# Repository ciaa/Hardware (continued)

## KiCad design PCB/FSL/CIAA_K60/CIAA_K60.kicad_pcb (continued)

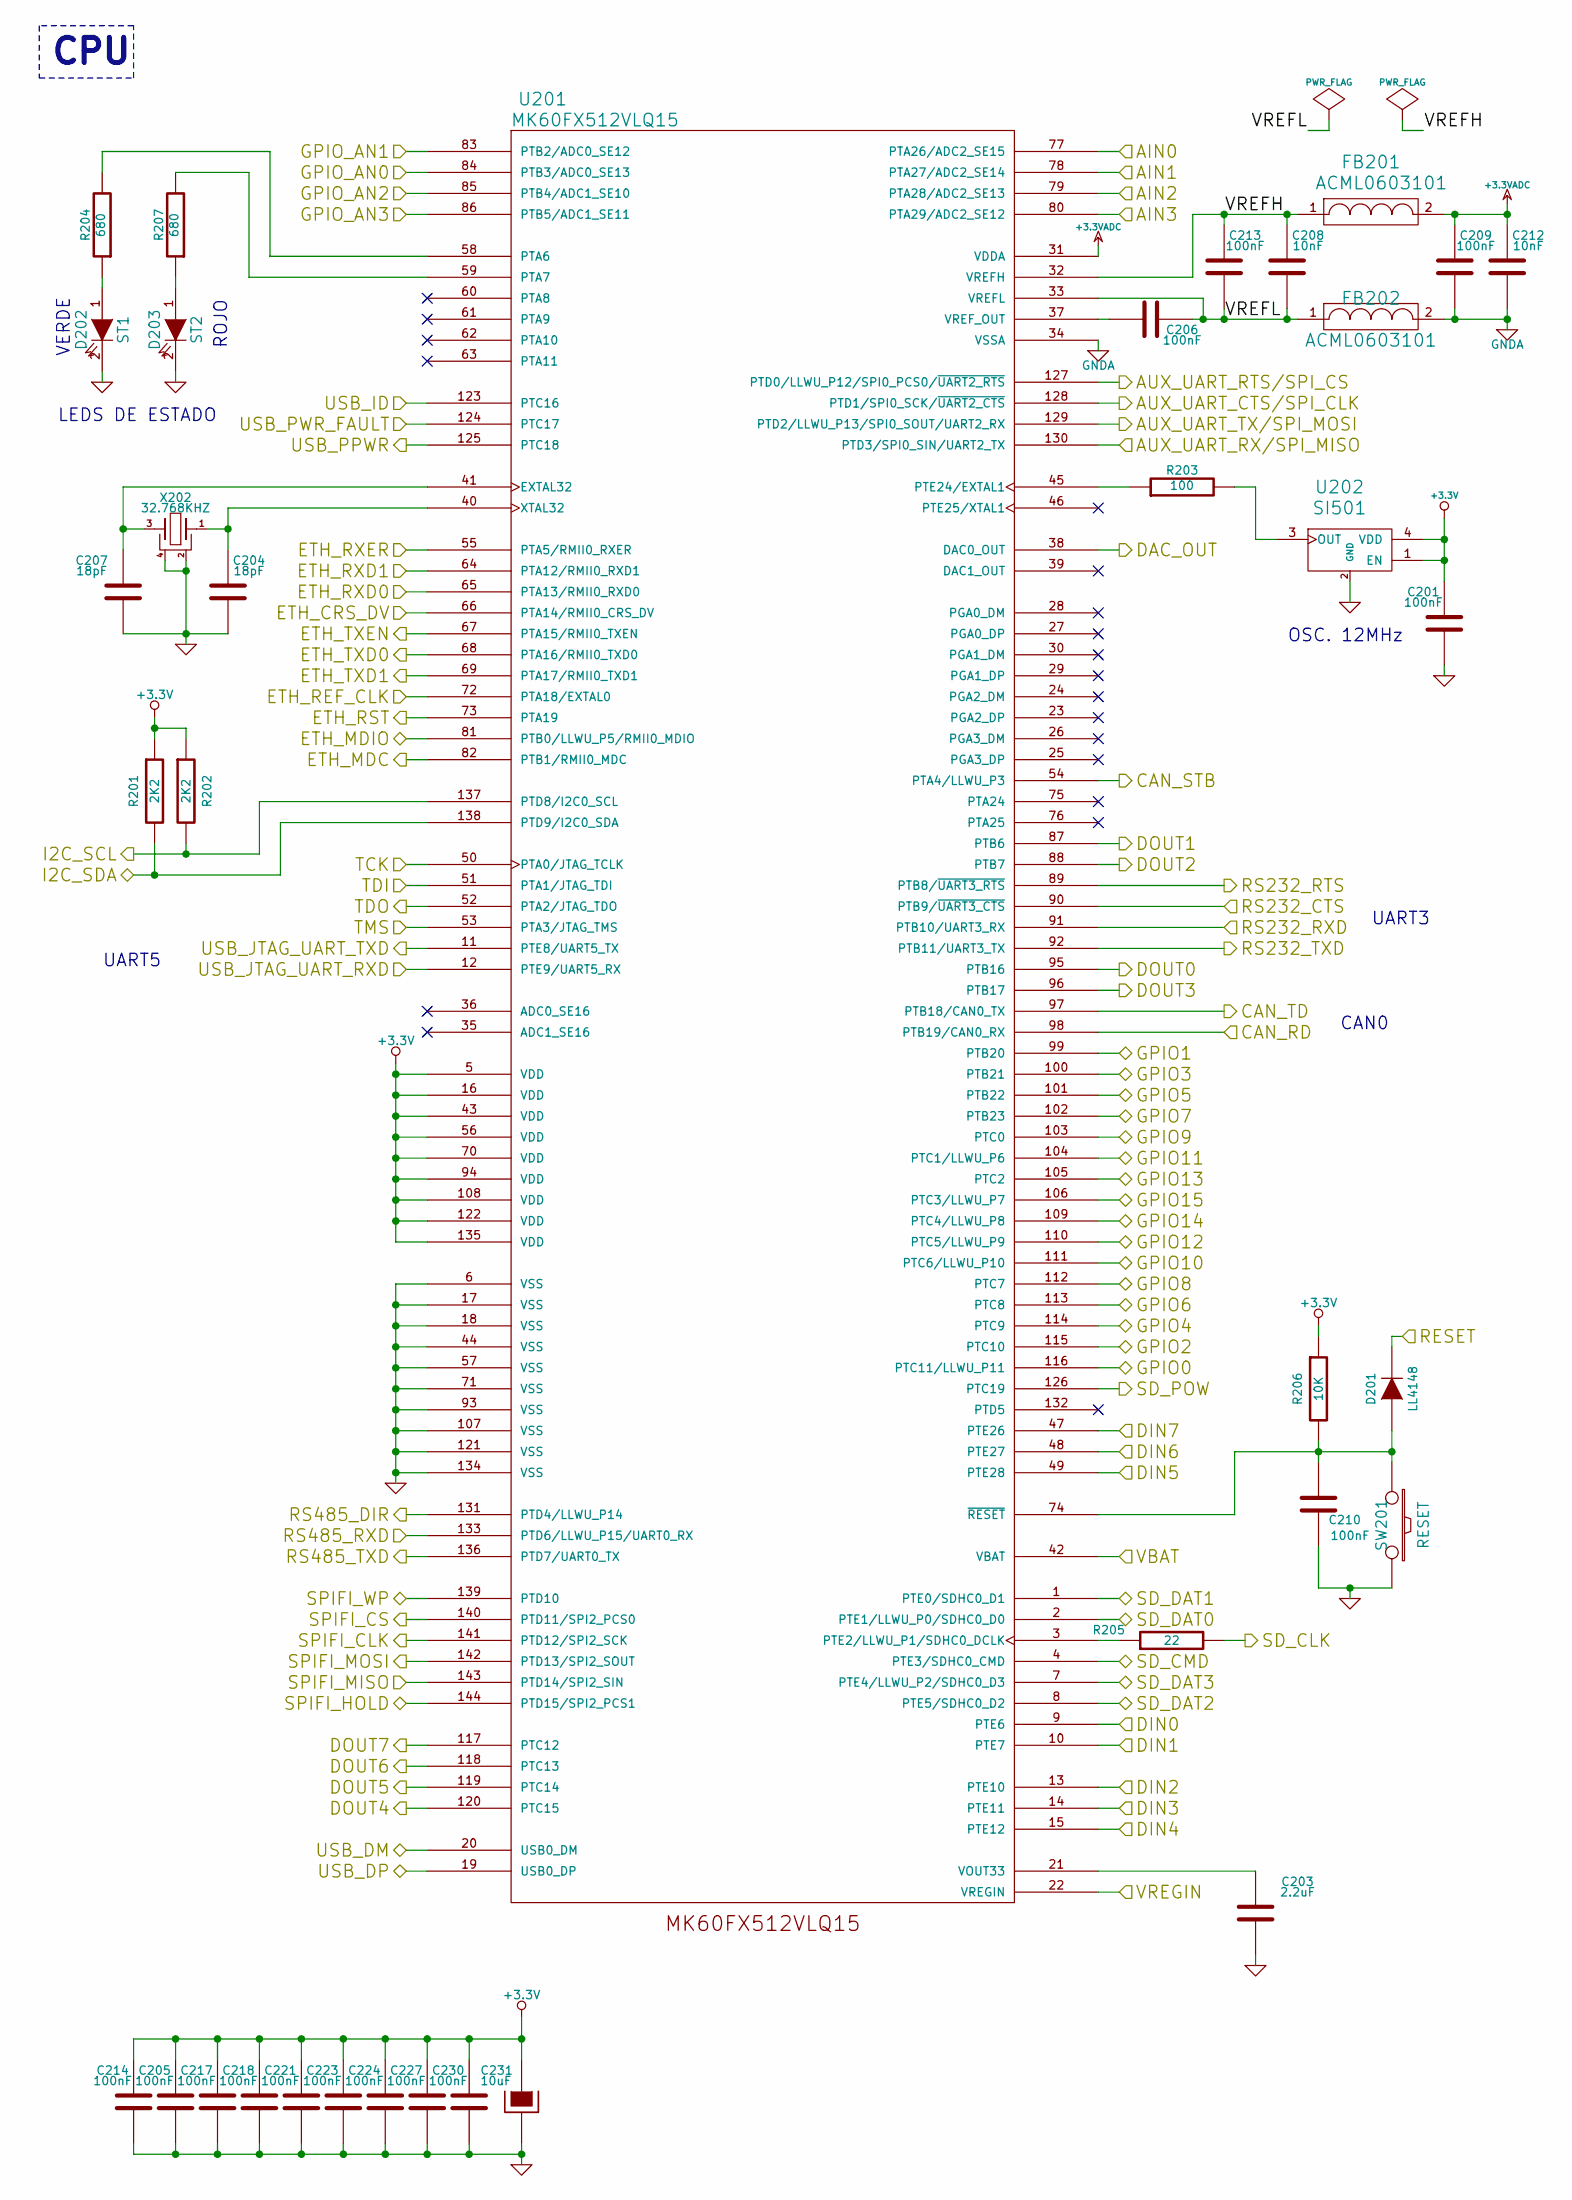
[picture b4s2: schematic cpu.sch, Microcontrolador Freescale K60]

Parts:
C201, C205, C206, C209, C210, C213, C214, C217, C218, C221, C223, C224, C227, C230: 100nF; c_0603; Digikey# 399-1096-1-ND
C203: 2.2uF; c_0603; Digikey# 587-2983-1-ND
C204, C207: 18pF; c_0603; Digikey# 399-1052-1-ND
C208, C212: 10nF; c_0603; Digikey# 399-1091-1-ND
C231: 10uF; c_1206POL; Digikey# 399-10116-1-ND
D201: LL4148; SOD-123; Digikey# LL4148FSCT-ND
D202: ST1; LED-0603; Digikey# 1080-1399-1-ND
D203: ST2; LED-0603; Digikey# 1080-1400-1-ND
FB201, FB202: ACML0603101; fb_0603; Digikey# ACML-0603-101-TCT-ND
R201, R202: 2K2; r_0603; Digikey# 311-2.2KGRCT-ND
R203: 100; r_0603; Digikey# 311-100GRCT-ND
R204, R207: 680; r_0603; Digikey# 311-680GRCT-ND
R205: 22; r_0603; Digikey# 311-22GRCT-ND
R206: 10K; r_0603; Digikey# 311-10KGRCT-ND
SW201: RESET; TACT_SMD_4; Digikey# 2-1437565-9
U201: MK60FX512VLQ15; LQFP144; Digikey# MK60FX512VLQ15-ND
U202: SI501; SI501_C; Digikey# 336-2889-ND
X202: 32.768KHZ; 4SOJ; Digikey# 535-9166-1-ND

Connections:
+3.3VADC: C209.1, C212.2, FB201.2, U201.31 (VDDA); also elsewhere on the board
/CPU/AIN0: U201.77 (PTA26/ADC2_SE15); also elsewhere on the board
/CPU/AIN1: U201.78 (PTA27/ADC2_SE14); also elsewhere on the board
/CPU/AIN2: U201.79 (PTA28/ADC2_SE13); also elsewhere on the board
/CPU/AIN3: U201.80 (PTA29/ADC2_SE12); also elsewhere on the board
/CPU/AUX_UART_CTS/SPI_CLK: U201.128 (PTD1/SPI0_SCK/~UART2_CTS); also elsewhere on the board
/CPU/AUX_UART_RTS/SPI_CS: U201.127 (PTD0/LLWU_P12/SPI0_PCS0/~UART2_RTS); also elsewhere on the board
/CPU/AUX_UART_RX/SPI_MISO: U201.130 (PTD3/SPI0_SIN/UART2_TX); also elsewhere on the board
/CPU/AUX_UART_TX/SPI_MOSI: U201.129 (PTD2/LLWU_P13/SPI0_SOUT/UART2_RX); also elsewhere on the board
/CPU/CAN_RD: U201.98 (PTB19/CAN0_RX); also elsewhere on the board
/CPU/CAN_STB: U201.54 (PTA4/LLWU_P3); also elsewhere on the board
/CPU/CAN_TD: U201.97 (PTB18/CAN0_TX); also elsewhere on the board
/CPU/DAC_OUT: U201.38 (DAC0_OUT); also elsewhere on the board
/CPU/DIN0: U201.9 (PTE6); also elsewhere on the board
/CPU/DIN1: U201.10 (PTE7); also elsewhere on the board
/CPU/DIN2: U201.13 (PTE10); also elsewhere on the board
/CPU/DIN3: U201.14 (PTE11); also elsewhere on the board
/CPU/DIN4: U201.15 (PTE12); also elsewhere on the board
/CPU/DIN5: U201.49 (PTE28); also elsewhere on the board
/CPU/DIN6: U201.48 (PTE27); also elsewhere on the board
/CPU/DIN7: U201.47 (PTE26); also elsewhere on the board
/CPU/DOUT0: U201.95 (PTB16); also elsewhere on the board
/CPU/DOUT1: U201.87 (PTB6); also elsewhere on the board
/CPU/DOUT2: U201.88 (PTB7); also elsewhere on the board
/CPU/DOUT3: U201.96 (PTB17); also elsewhere on the board
/CPU/DOUT4: U201.120 (PTC15); also elsewhere on the board
/CPU/DOUT5: U201.119 (PTC14); also elsewhere on the board
/CPU/DOUT6: U201.118 (PTC13); also elsewhere on the board
/CPU/DOUT7: U201.117 (PTC12); also elsewhere on the board
/CPU/ETH_CRS_DV: U201.66 (PTA14/RMII0_CRS_DV); also elsewhere on the board
/CPU/ETH_MDC: U201.82 (PTB1/RMII0_MDC); also elsewhere on the board
/CPU/ETH_MDIO: U201.81 (PTB0/LLWU_P5/RMII0_MDIO); also elsewhere on the board
/CPU/ETH_REF_CLK: U201.72 (PTA18/EXTAL0); also elsewhere on the board
/CPU/ETH_RST: U201.73 (PTA19); also elsewhere on the board
/CPU/ETH_RXD0: U201.65 (PTA13/RMII0_RXD0); also elsewhere on the board
/CPU/ETH_RXD1: U201.64 (PTA12/RMII0_RXD1); also elsewhere on the board
/CPU/ETH_RXER: U201.55 (PTA5/RMII0_RXER); also elsewhere on the board
/CPU/ETH_TXD0: U201.68 (PTA16/RMII0_TXD0); also elsewhere on the board
/CPU/ETH_TXD1: U201.69 (PTA17/RMII0_TXD1); also elsewhere on the board
/CPU/ETH_TXEN: U201.67 (PTA15/RMII0_TXEN); also elsewhere on the board
/CPU/GPIO0: U201.116 (PTC11/LLWU_P11); also elsewhere on the board
/CPU/GPIO1: U201.99 (PTB20); also elsewhere on the board
/CPU/GPIO2: U201.115 (PTC10); also elsewhere on the board
/CPU/GPIO3: U201.100 (PTB21); also elsewhere on the board
/CPU/GPIO4: U201.114 (PTC9); also elsewhere on the board
/CPU/GPIO5: U201.101 (PTB22); also elsewhere on the board
/CPU/GPIO6: U201.113 (PTC8); also elsewhere on the board
/CPU/GPIO7: U201.102 (PTB23); also elsewhere on the board
/CPU/GPIO8: U201.112 (PTC7); also elsewhere on the board
/CPU/GPIO9: U201.103 (PTC0); also elsewhere on the board
/CPU/GPIO10: U201.111 (PTC6/LLWU_P10); also elsewhere on the board
/CPU/GPIO11: U201.104 (PTC1/LLWU_P6); also elsewhere on the board
/CPU/GPIO12: U201.110 (PTC5/LLWU_P9); also elsewhere on the board
/CPU/GPIO13: U201.105 (PTC2); also elsewhere on the board
/CPU/GPIO14: U201.109 (PTC4/LLWU_P8); also elsewhere on the board
/CPU/GPIO15: U201.106 (PTC3/LLWU_P7); also elsewhere on the board
/CPU/I2C_SCL: R202.2, U201.137 (PTD8/I2C0_SCL); also elsewhere on the board
/CPU/I2C_SDA: R201.2, U201.138 (PTD9/I2C0_SDA); also elsewhere on the board
/CPU/RESET: D201.2 (K); also elsewhere on the board
/CPU/RS232_CTS: U201.90 (PTB9/~UART3_CTS); also elsewhere on the board
/CPU/RS232_RTS: U201.89 (PTB8/~UART3_RTS); also elsewhere on the board
/CPU/RS232_RXD: U201.91 (PTB10/UART3_RX); also elsewhere on the board
/CPU/RS232_TXD: U201.92 (PTB11/UART3_TX); also elsewhere on the board
/CPU/RS485_DIR: U201.131 (PTD4/LLWU_P14); also elsewhere on the board
/CPU/RS485_RXD: U201.133 (PTD6/LLWU_P15/UART0_RX); also elsewhere on the board
/CPU/RS485_TXD: U201.136 (PTD7/UART0_TX); also elsewhere on the board
/CPU/SD_CLK: R205.2; also elsewhere on the board
/CPU/SD_CMD: U201.4 (PTE3/SDHC0_CMD); also elsewhere on the board
/CPU/SD_DAT0: U201.2 (PTE1/LLWU_P0/SDHC0_D0); also elsewhere on the board
/CPU/SD_DAT1: U201.1 (PTE0/SDHC0_D1); also elsewhere on the board
/CPU/SD_DAT2: U201.8 (PTE5/SDHC0_D2); also elsewhere on the board
/CPU/SD_DAT3: U201.7 (PTE4/LLWU_P2/SDHC0_D3); also elsewhere on the board
/CPU/SD_POW: U201.126 (PTC19); also elsewhere on the board
/CPU/SPIFI_CLK: U201.141 (PTD12/SPI2_SCK); also elsewhere on the board
/CPU/SPIFI_CS: U201.140 (PTD11/SPI2_PCS0); also elsewhere on the board
/CPU/SPIFI_HOLD: U201.144 (PTD15/SPI2_PCS1); also elsewhere on the board
/CPU/SPIFI_MISO: U201.143 (PTD14/SPI2_SIN); also elsewhere on the board
/CPU/SPIFI_MOSI: U201.142 (PTD13/SPI2_SOUT); also elsewhere on the board
/CPU/SPIFI_WP: U201.139 (PTD10); also elsewhere on the board
/CPU/TCK: U201.50 (PTA0/JTAG_TCLK); also elsewhere on the board
/CPU/TDI: U201.51 (PTA1/JTAG_TDI); also elsewhere on the board
/CPU/TDO: U201.52 (PTA2/JTAG_TDO); also elsewhere on the board
/CPU/TMS: U201.53 (PTA3/JTAG_TMS); also elsewhere on the board
/CPU/USB_DM: U201.20 (USB0_DM); also elsewhere on the board
/CPU/USB_DP: U201.19 (USB0_DP); also elsewhere on the board
/CPU/USB_ID: U201.123 (PTC16); also elsewhere on the board
/CPU/USB_JTAG_UART_RXD: U201.12 (PTE9/UART5_RX); also elsewhere on the board
/CPU/USB_JTAG_UART_TXD: U201.11 (PTE8/UART5_TX); also elsewhere on the board
/CPU/VBAT: U201.42 (VBAT); also elsewhere on the board
/CPU/VREFH: C208.2, C213.1, FB201.1, U201.32 (VREFH)
/CPU/VREFL: C206.2, C208.1, C213.2, FB202.1, U201.33 (VREFL)
/Fuente/USB_VBUS: U201.22 (VREGIN); also elsewhere on the board
/GPIO/AN0: U201.84 (PTB3/ADC0_SE13); also elsewhere on the board
/GPIO/AN1: U201.83 (PTB2/ADC0_SE12); also elsewhere on the board
/GPIO/AN2: U201.85 (PTB4/ADC1_SE10); also elsewhere on the board
/GPIO/AN3: U201.86 (PTB5/ADC1_SE11); also elsewhere on the board
/USB OTG/USB0_PPWR: U201.125 (PTC18); also elsewhere on the board
/USB OTG/USB0_PWR_FAULT: U201.124 (PTC17); also elsewhere on the board
GND: C201.2, C203.2, C204.2, C205.2, C207.2, C210.1, C214.2, C217.2, C218.2, C221.2, C223.2, C224.2, C227.2, C230.2, C231.2, D202.2 (K), D203.2 (K), SW201.2, U201.6 (VSS), U201.17 (VSS), U201.18 (VSS), U201.44 (VSS), U201.57 (VSS), U201.71 (VSS), U201.93 (VSS), U201.107 (VSS), U201.121 (VSS), U201.134 (VSS), U202.2 (GND), X202.2 (GND), X202.4 (GND); also elsewhere on the board
GNDA: C209.2, C212.1, FB202.2, U201.34 (VSSA); also elsewhere on the board
unnamed: C207.1, U201.41 (EXTAL32), X202.3 (B)
unnamed: C204.1, U201.40 (XTAL32), X202.1 (A)
unnamed: C210.2, D201.1 (A), R206.2, SW201.1, U201.74 (~RESET)
unnamed: C203.1, U201.21 (VOUT33)
unnamed: D202.1 (A), R204.1
unnamed: D203.1 (A), R207.1
unnamed: R207.2, U201.59 (PTA7)
unnamed: R204.2, U201.58 (PTA6)
unnamed: R203.1, U201.45 (PTE24/EXTAL1)
unnamed: R203.2, U202.3 (OUT)
unnamed: C206.1, U201.37 (VREF_OUT)
unnamed: R205.1, U201.3 (PTE2/LLWU_P1/SDHC0_DCLK)

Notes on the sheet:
CPU
VERDE
ROJO
LEDS DE ESTADO
CAN0
UART3
UART5
OSC. 12MHz

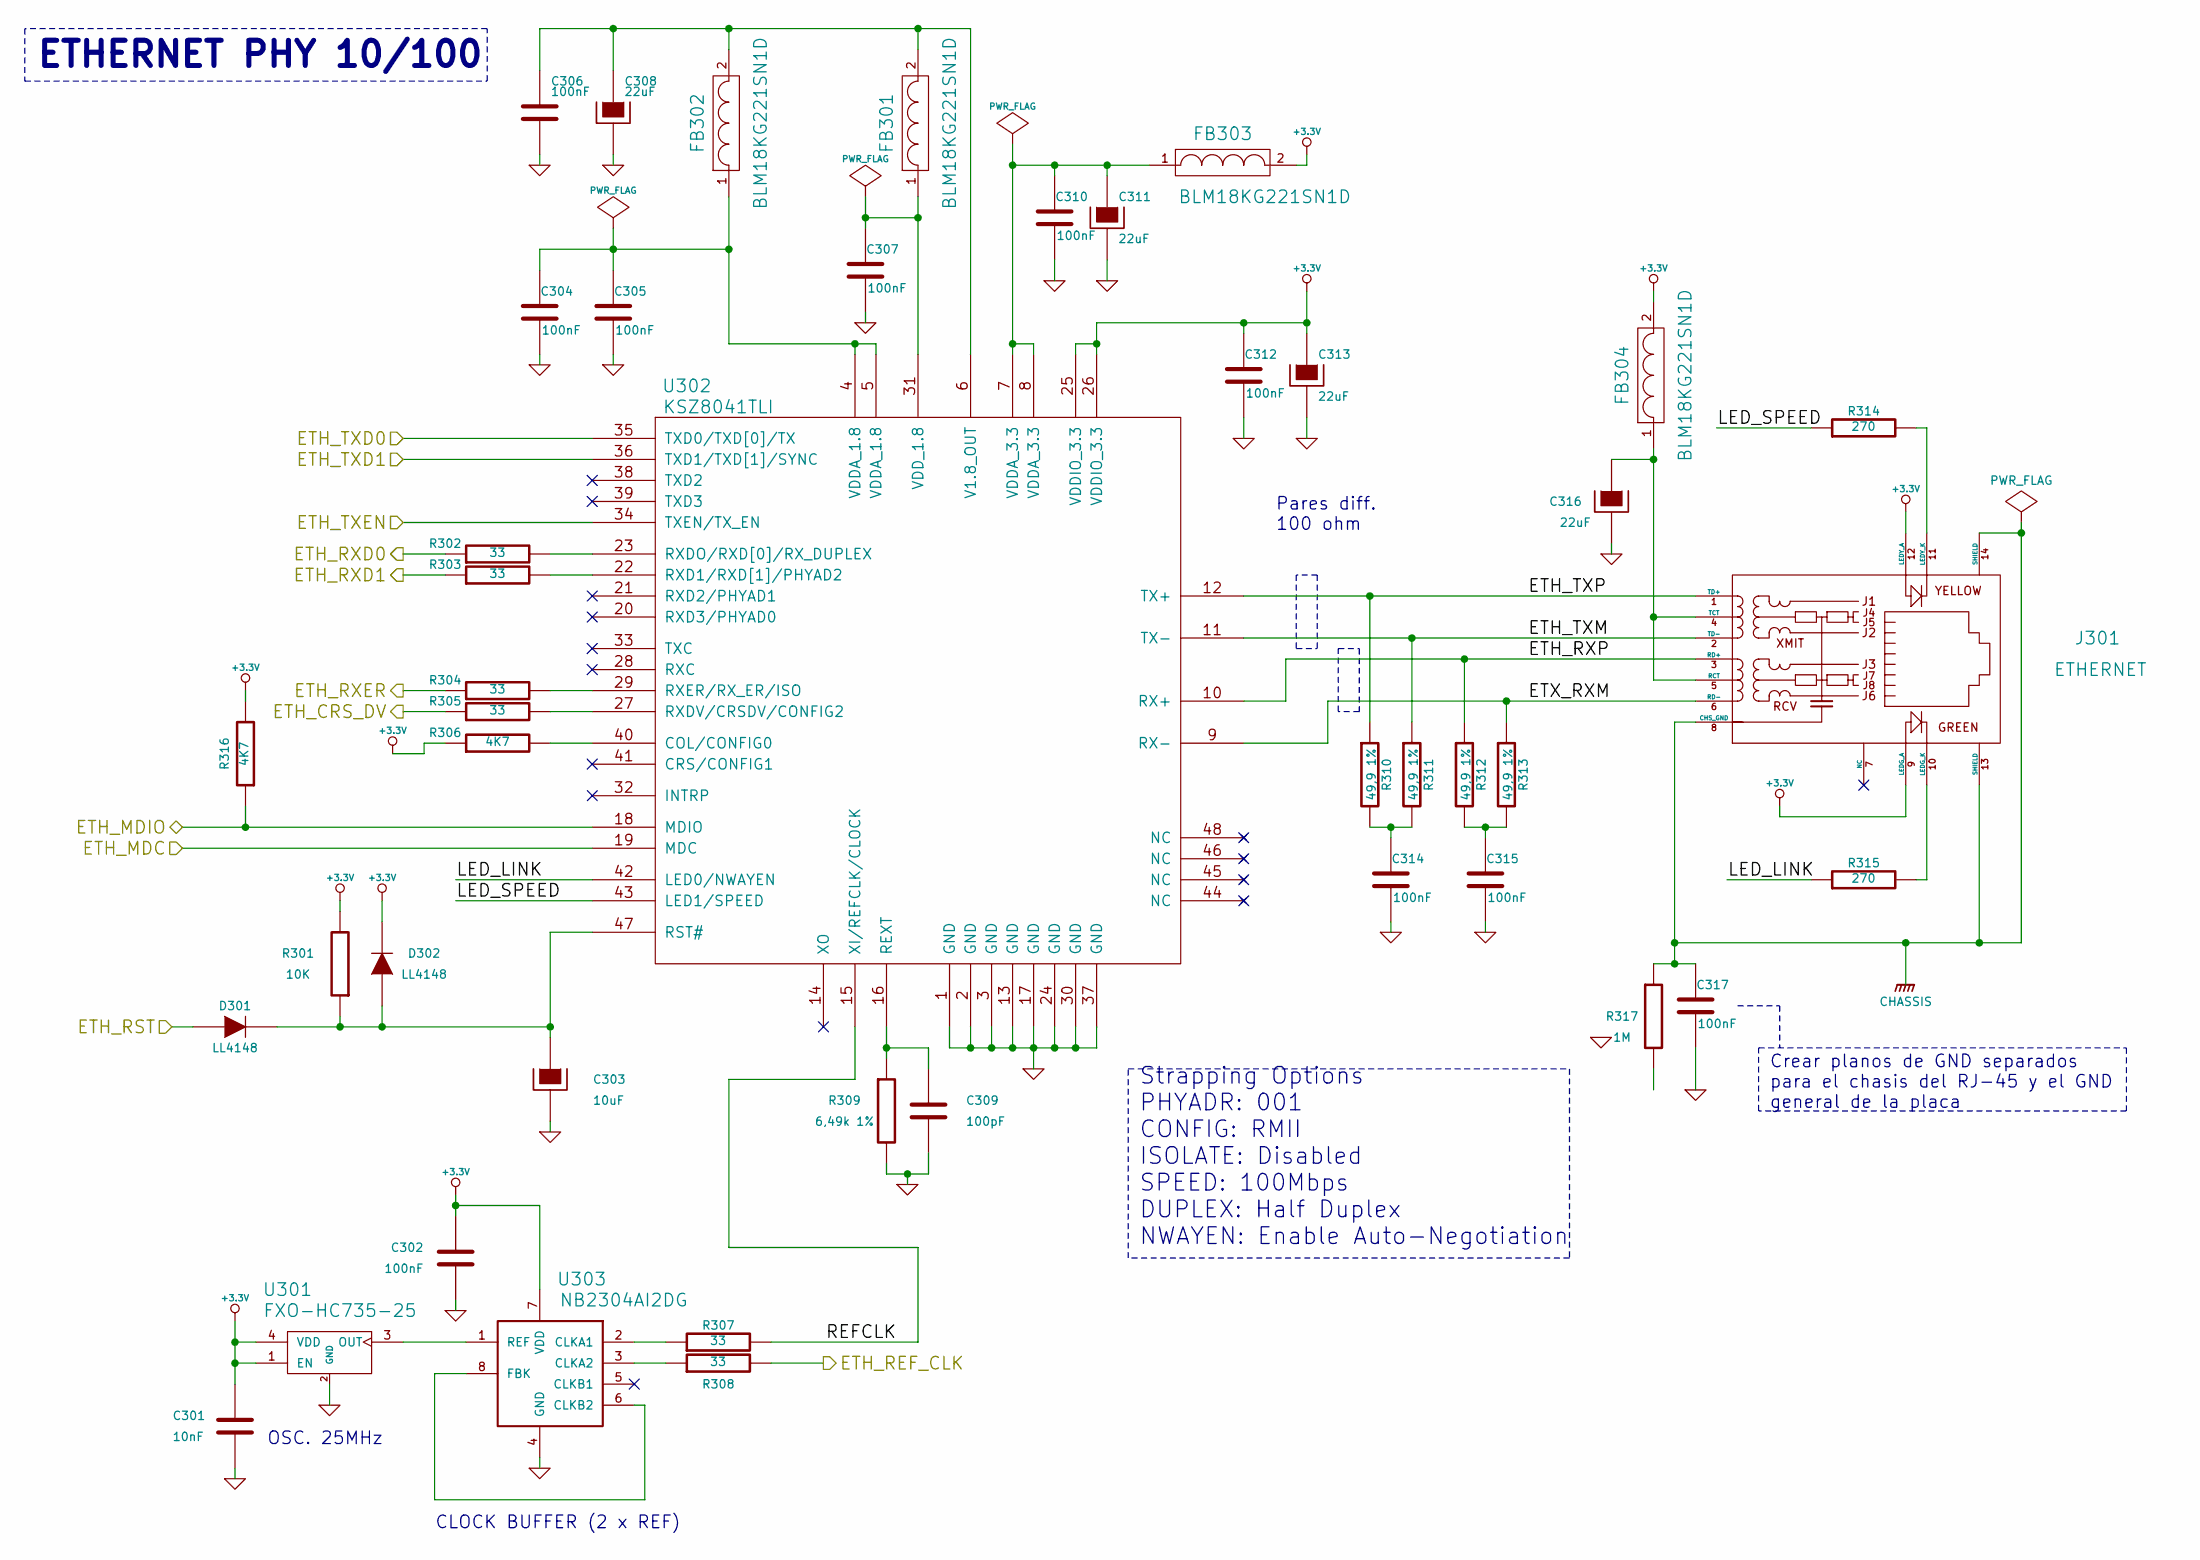
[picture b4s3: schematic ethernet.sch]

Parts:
C301: 10nF; c_0603; Digikey# 399-1091-1-ND
C302, C304, C305, C306, C307, C310, C312, C314, C315, C317: 100nF; c_0603; Digikey# 399-1096-1-ND
C303: 10uF; c_1206POL; Digikey# 399-10116-1-ND
C308, C311, C313, C316: 22uF; c_1206POL; Digikey# 399-8279-1-ND
C309: 100pF; c_0603; Digikey# 399-7824-1-ND
D301, D302: LL4148; SOD-123; Digikey# LL4148FSCT-ND
FB301, FB302, FB303, FB304: BLM18KG221SN1D; fb_0603; Digikey# 490-5255-1-ND
J301: ETHERNET; RJ45_Pulse_J403-A; Digikey# 553-1483-ND
R301: 10K; r_0603; Digikey# 311-10KGRCT-ND
R302, R303, R304, R305, R307, R308: 33; r_0603; Digikey# CR0603-JW-330GLFCT-ND
R306, R316: 4K7; r_0603; Digikey# 311-4.7KGRCT-ND
R309: 6,49k 1%; r_0603; Digikey# 311-6.49KHRCT-ND
R310, R311, R312, R313: 49,9 1%; r_0603; Digikey# 311-49.9HRCT-ND
R314, R315: 270; r_0603; Digikey# 311-270GRCT-ND
R317: 1M; r_0603; Digikey# 311-1.0MGRCT-ND
U301: FXO-HC735-25; FXODFN4; Digikey# 631-1055-1-ND
U302: KSZ8041TLI; TQFP48; Digikey# 576-2971-5-ND
U303: NB2304AI2DG; SOIC-8; Digikey# NB2304AI2DGOS-ND

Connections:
/CPU/ETH_CRS_DV: R305.1; also elsewhere on the board
/CPU/ETH_MDC: U302.19 (MDC); also elsewhere on the board
/CPU/ETH_MDIO: R316.1, U302.18 (MDIO); also elsewhere on the board
/CPU/ETH_REF_CLK: R308.2; also elsewhere on the board
/CPU/ETH_RST: D301.1 (A); also elsewhere on the board
/CPU/ETH_RXD0: R302.1; also elsewhere on the board
/CPU/ETH_RXD1: R303.1; also elsewhere on the board
/CPU/ETH_RXER: R304.1; also elsewhere on the board
/CPU/ETH_TXD0: U302.35 (TXD0/TXD[0]/TX); also elsewhere on the board
/CPU/ETH_TXD1: U302.36 (TXD1/TXD[1]/SYNC); also elsewhere on the board
/CPU/ETH_TXEN: U302.34 (TXEN/TX_EN); also elsewhere on the board
/Ethernet/ETH_RXP: J301.3 (RD+), R312.1, U302.10 (RX+)
/Ethernet/ETH_TXM: J301.2 (TD-), R311.1, U302.11 (TX-)
/Ethernet/ETH_TXP: J301.1 (TD+), R310.1, U302.12 (TX+)
/Ethernet/ETX_RXM: J301.6 (RD-), R313.1, U302.9 (RX-)
/Ethernet/LED_LINK: R315.1, U302.42 (LED0/NWAYEN)
/Ethernet/LED_SPEED: R314.1, U302.43 (LED1/SPEED)
/Ethernet/REFCLK: R307.2, U302.15 (XI/REFCLK/CLOCK)
GND: C301.2, C302.1, C303.2, C304.2, C305.2, C306.2, C307.2, C308.2, C309.2, C310.2, C311.2, C312.2, C313.2, C314.2, C315.2, C316.2, C317.2, R309.2, R317.2, U301.2 (GND), U302.1 (GND), U302.2 (GND), U302.3 (GND), U302.13 (GND), U302.17 (GND), U302.24 (GND), U302.30 (GND), U302.37 (GND), U303.4 (GND); also elsewhere on the board
GNDPWR: C317.1, J301.8 (CHS_GND), J301.13 (SHIELD), J301.14 (SHIELD), R317.1; also elsewhere on the board
unnamed: R307.1, U303.2 (CLKA1)
unnamed: C316.1, FB304.1, J301.4 (TCT), J301.5 (RCT)
unnamed: J301.10 (LEDG_K), R315.2
unnamed: R308.1, U303.3 (CLKA2)
unnamed: C309.1, R309.1, U302.16 (REXT)
unnamed: C315.1, R312.2, R313.2
unnamed: C314.1, R310.2, R311.2
unnamed: U303.6 (CLKB2), U303.8 (FBK)
unnamed: U301.3 (OUT), U303.1 (REF)
unnamed: R305.2, U302.27 (RXDV/CRSDV/CONFIG2)
unnamed: R304.2, U302.29 (RXER/RX_ER/ISO)
unnamed: C310.1, C311.1, FB303.1, U302.7 (VDDA_3.3), U302.8 (VDDA_3.3)
unnamed: R303.2, U302.22 (RXD1/RXD[1]/PHYAD2)
unnamed: R306.2, U302.40 (COL/CONFIG0)
unnamed: R302.2, U302.23 (RXDO/RXD[0]/RX_DUPLEX)
unnamed: J301.11 (LEDY_K), R314.2
unnamed: C303.1, D301.2 (K), D302.1 (A), R301.1, U302.47 (RST#)
unnamed: C304.1, C305.1, FB302.1, U302.4 (VDDA_1.8), U302.5 (VDDA_1.8)
unnamed: C307.1, FB301.1, U302.31 (VDD_1.8)
unnamed: C306.1, C308.1, FB301.2, FB302.2, U302.6 (V1.8_OUT)

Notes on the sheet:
Strapping Options PHYADR: 001 CONFIG: RMII ISOLATE: Disabled SPEED: 100Mbps DUPLEX: Half Duplex NWAYEN: Enable Auto-Negotiation
Crear planos de GND separados para el chasis del RJ-45 y el GND general de la placa
ETHERNET PHY 10/100
OSC. 25MHz
CLOCK BUFFER (2 x REF)
Pares diff. 100 ohm

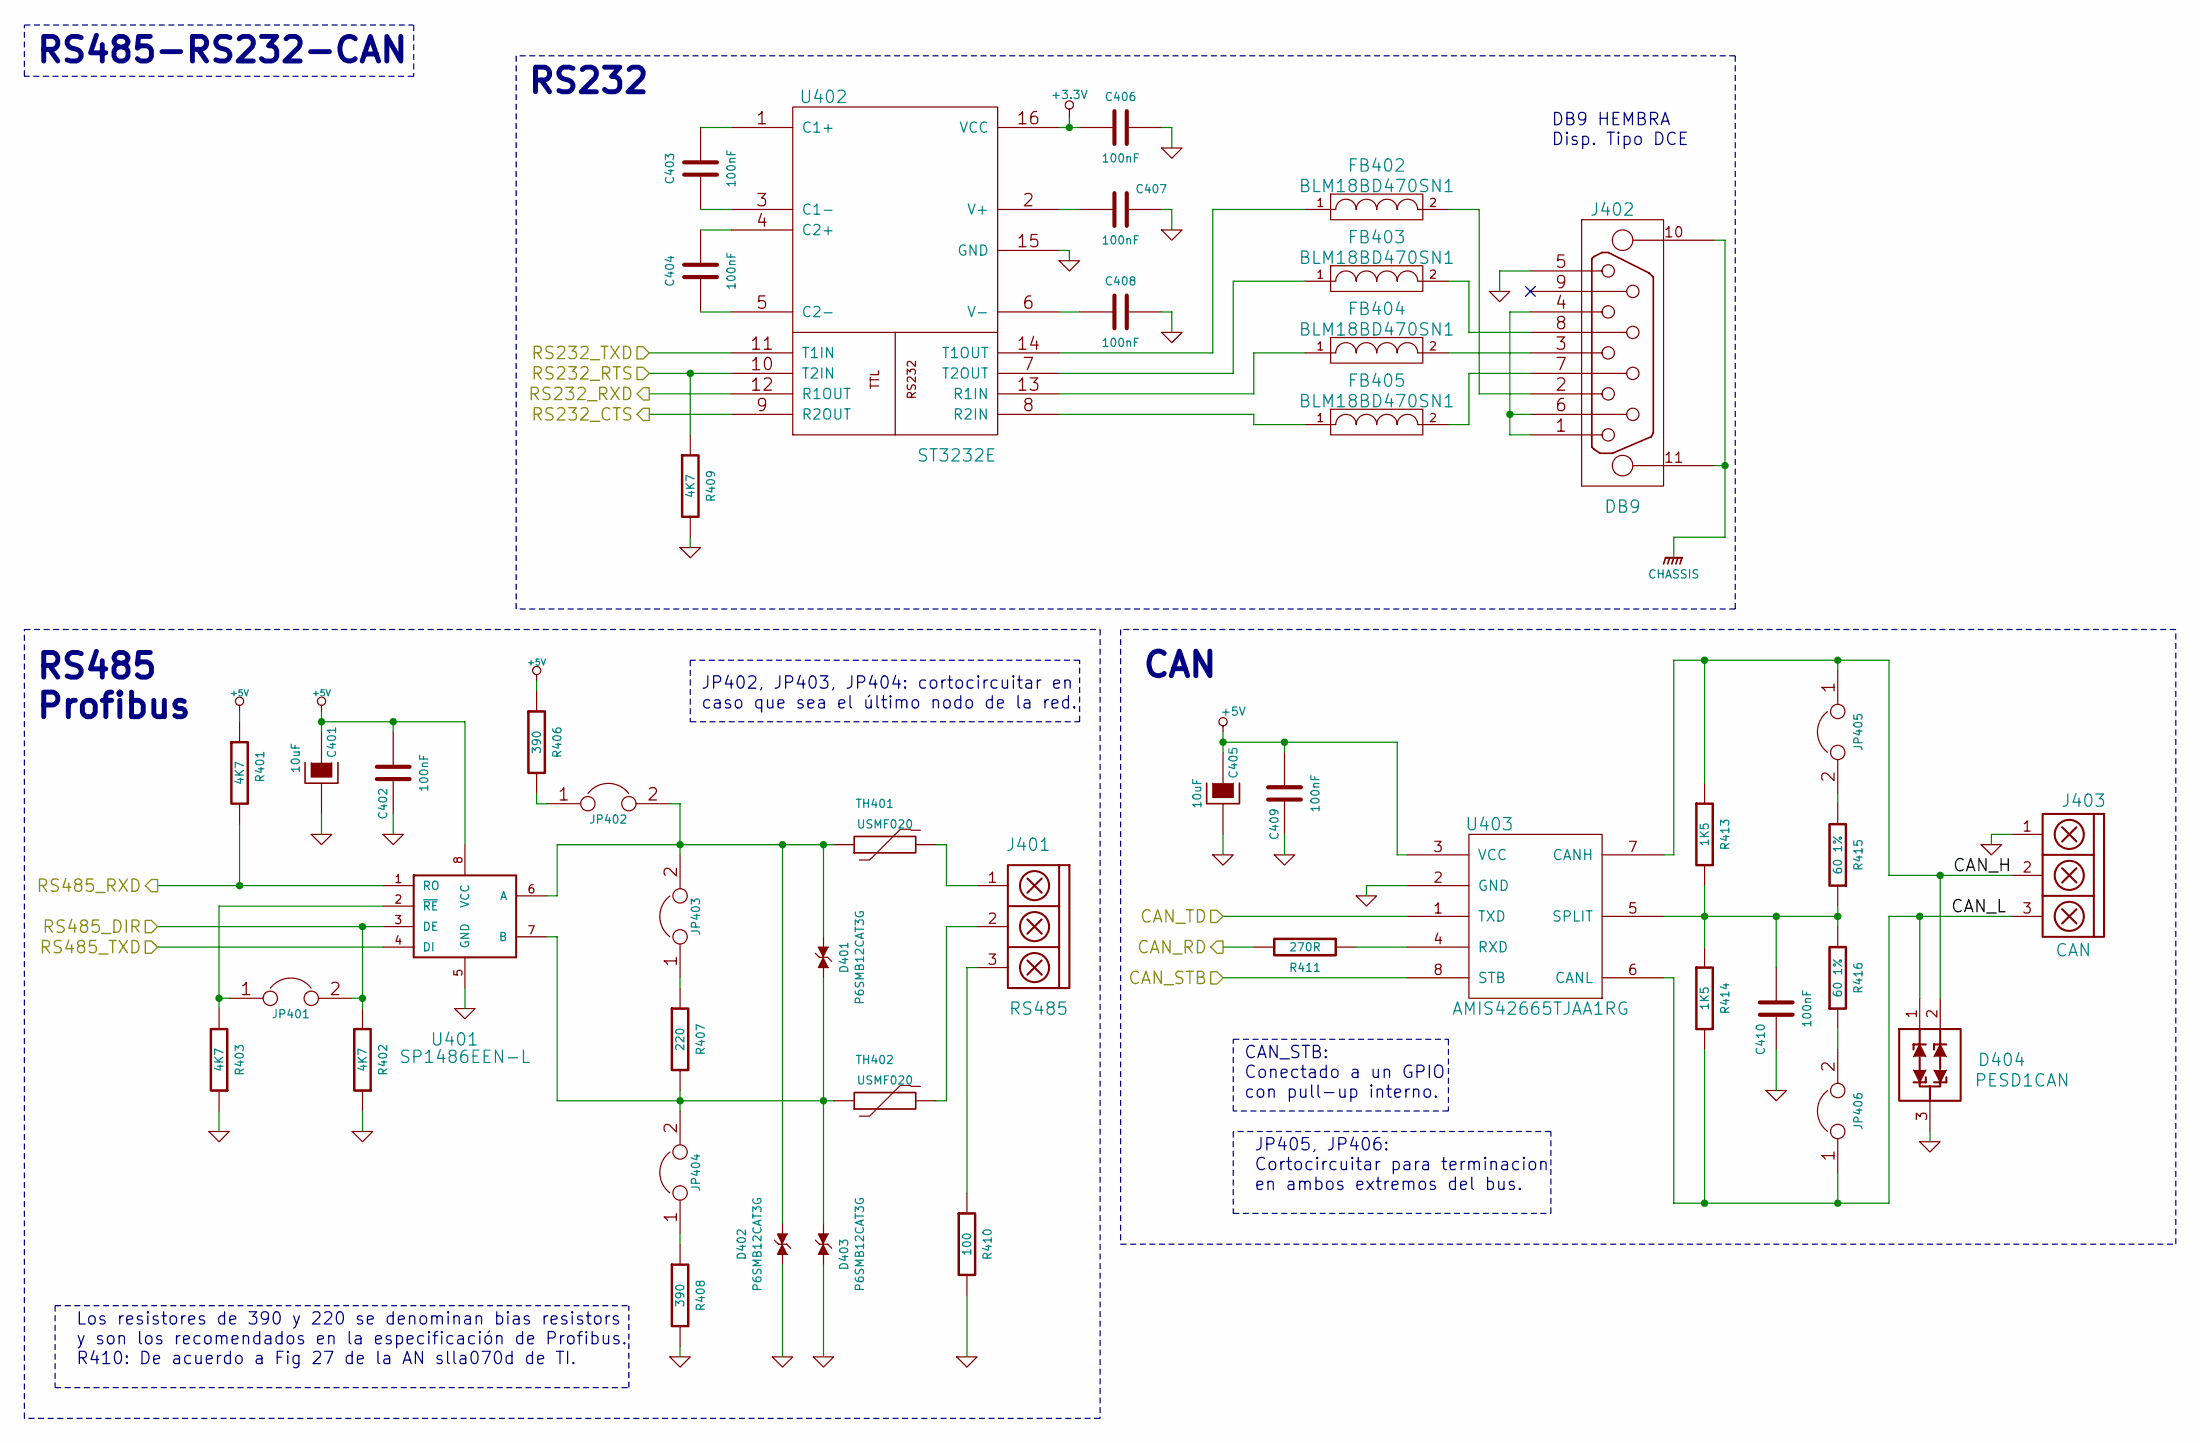
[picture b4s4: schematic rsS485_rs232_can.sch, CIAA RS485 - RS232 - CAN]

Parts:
C401, C405: 10uF; c_1206POL; Digikey# 399-10116-1-ND
C402, C403, C404, C406, C407, C408, C409, C410: 100nF; c_0603; Digikey# 399-1096-1-ND
D401, D402, D403: P6SMB12CAT3G; DO-214AA_SMB; Digikey# P6SMB12CAT3GOSCT-ND
D404: PESD1CAN; SOT-23; Digikey# 568-4032-1-ND
FB402, FB403, FB404, FB405: BLM18BD470SN1; fb_0603; Digikey# 490-5211-1-ND
J401: RS485; bornier3; Digikey# 571-7969493
J402: DB9; DB9_F_TH; Digikey# S9554-ND
J403: CAN; bornier3; Digikey# 571-7969493
JP401, JP402, JP403, JP404, JP405, JP406: JUMPER; PIN_ARRAY_2x1; Digikey# S1212EC-40-ND
R401, R402, R403, R409: 4K7; r_0603; Digikey# 311-4.7KGRCT-ND
R406, R408: 390; r_0603; Digikey# 311-390GRCT-ND
R407: 220; r_0603; Digikey# 311-220GRCT-ND
R410: 100; r_2010; Digikey# CR2010-JW-101ELFCT-ND
R411: 270R; r_0603; Digikey# 311-270GRCT-ND
R413, R414: 1K5; r_0603; Digikey# 311-1.5KGRCT-ND
R415, R416: 60 1%; r_0603; Digikey# 311-59.0HRCT-ND
TH401, TH402: USMF020; ptc_1210; Digikey# MF-USMF020-2CT-ND
U401: SP1486EEN-L; SOIC-8; Digikey# 1016-1003-5-ND
U402: ST3232E; TSSOP-16; Digikey# 497-6538-1-ND
U403: AMIS42665TJAA1RG; SOIC-8; Digikey# 766-1006-1-ND

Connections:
+5V: C401.1, C402.2, C405.1, C409.2, R401.1, R406.1, U401.8 (VCC), U403.3 (VCC); also elsewhere on the board
/CPU/CAN_RD: R411.2; also elsewhere on the board
/CPU/CAN_STB: U403.8 (STB); also elsewhere on the board
/CPU/CAN_TD: U403.1 (TXD); also elsewhere on the board
/CPU/RS232_CTS: U402.9 (R2OUT); also elsewhere on the board
/CPU/RS232_RTS: R409.1, U402.10 (T2IN); also elsewhere on the board
/CPU/RS232_RXD: U402.12 (R1OUT); also elsewhere on the board
/CPU/RS232_TXD: U402.11 (T1IN); also elsewhere on the board
/CPU/RS485_DIR: JP401.2, R402.2, U401.3 (DE); also elsewhere on the board
/CPU/RS485_RXD: R401.2, U401.1 (RO); also elsewhere on the board
/CPU/RS485_TXD: U401.4 (DI); also elsewhere on the board
/RS485_RS232_CAN/CAN_H: D404.2, J403.2, JP405.1, R413.1, U403.7 (CANH)
/RS485_RS232_CAN/CAN_L: D404.1, J403.3, JP406.1, R414.2, U403.6 (CANL)
GND: C401.2, C402.1, C405.2, C406.2, C407.2, C408.2, C409.1, C410.2, D402.2 (Anode), D403.2 (Anode), D404.3, J402.5 (Signal_Ground), J403.1, R402.1, R403.1, R408.2, R409.2, R410.2, U401.5 (GND), U402.15 (GND), U403.2 (GND); also elsewhere on the board
GNDPWR: J402.10 (chassis_pin), J402.11 (chassis_pin); also elsewhere on the board
unnamed: FB405.1, U402.8 (R2IN)
unnamed: FB405.2, J402.7 (RTS)
unnamed: FB404.1, U402.13 (R1IN)
unnamed: FB402.1, U402.14 (T1OUT)
unnamed: FB403.1, U402.7 (T2OUT)
unnamed: C408.1, U402.6 (V-)
unnamed: FB403.2, J402.8 (CTS)
unnamed: C404.1, U402.4 (C2+)
unnamed: C404.2, U402.5 (C2-)
unnamed: C407.1, U402.2 (V+)
unnamed: FB402.2, J402.2 (Receive_Data)
unnamed: JP404.1, R408.1
unnamed: FB404.2, J402.3 (Transmit_Data)
unnamed: J402.1 (Data_Carrier_Detect), J402.4 (DTR), J402.6 (DSR)
unnamed: JP402.1, R406.2
unnamed: R411.1, U403.4 (RXD)
unnamed: JP403.1, R407.1
unnamed: D401.1 (cathode), D402.1 (cathode), JP402.2, JP403.2, TH401.1, U401.6 (A)
unnamed: C403.1, U402.1 (C1+)
unnamed: C403.2, U402.3 (C1-)
unnamed: JP405.2, R415.2
unnamed: JP406.2, R416.1
unnamed: J401.1, TH401.2
unnamed: J401.2, TH402.2
unnamed: J401.3, R410.1
unnamed: JP401.1, R403.2, U401.2 (~RE~)
unnamed: C410.1, R413.2, R414.1, R415.1, R416.2, U403.5 (SPLIT)
unnamed: D401.2 (Anode), D403.1 (cathode), JP404.2, R407.2, TH402.1, U401.7 (B)

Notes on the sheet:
RS232
RS485 Profibus
CAN
JP405, JP406: Cortocircuitar para terminacion en ambos extremos del bus.
JP402, JP403, JP404: cortocircuitar en caso que sea el último nodo de la red.
RS485-RS232-CAN
DB9 HEMBRA Disp. Tipo DCE
Los resistores de 390 y 220 se denominan bias resistors y son los recomendados en la especificación de Profibus. R410: De acuerdo a Fig 27 de la AN slla070d de TI.
CAN_STB: Conectado a un GPIO con pull-up interno.

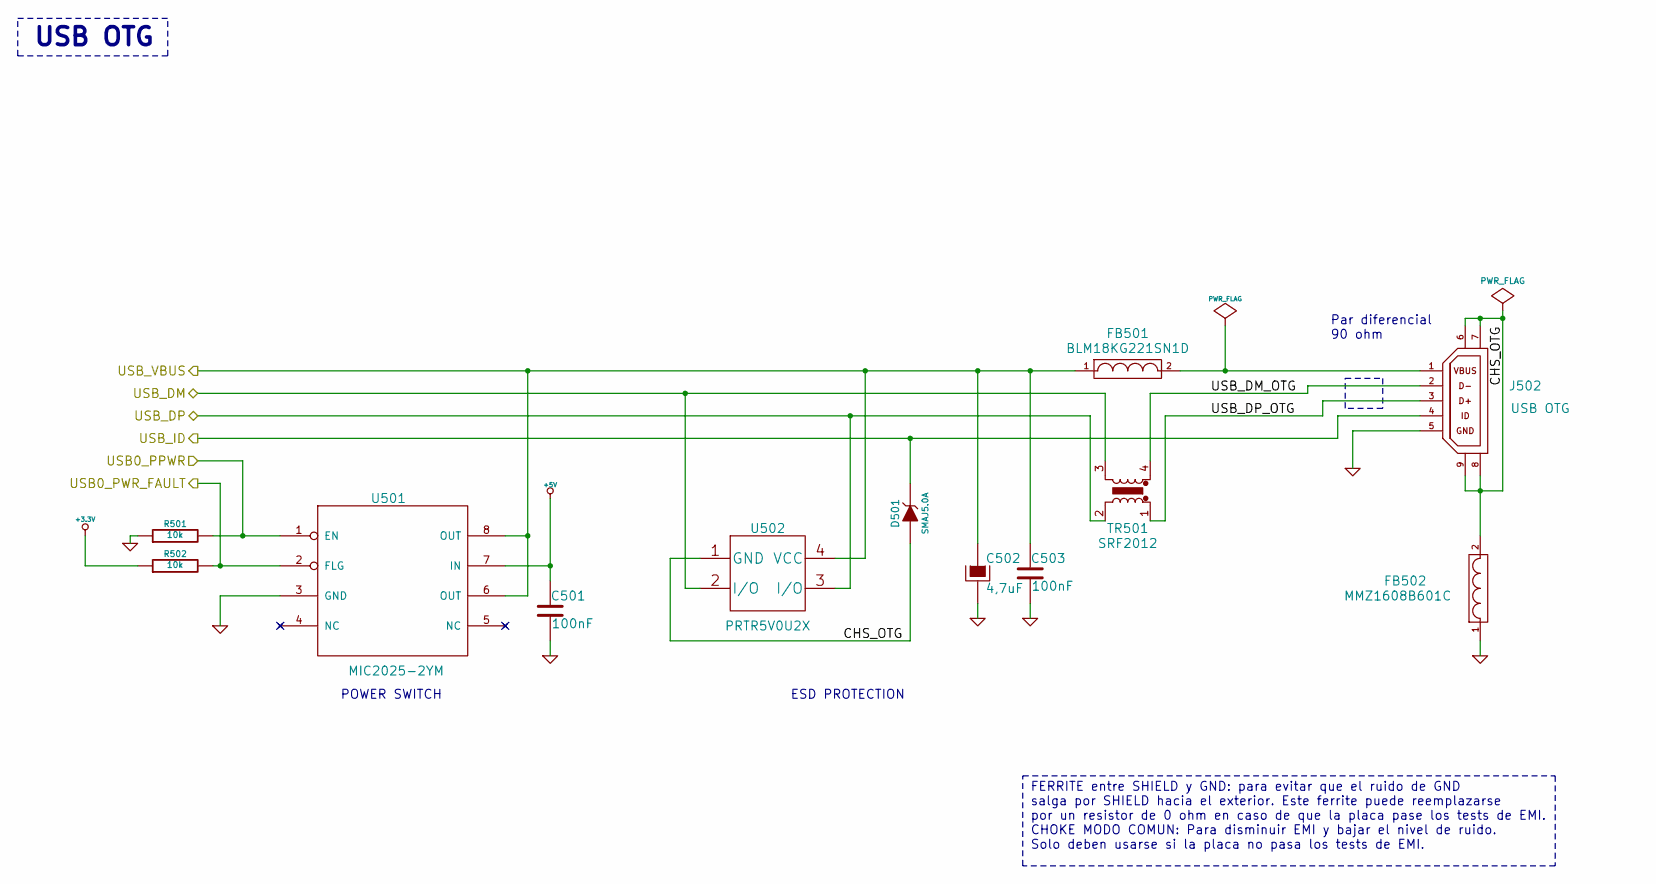
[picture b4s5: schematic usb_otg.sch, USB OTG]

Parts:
C501, C503: 100nF; c_0603; Digikey# 399-1096-1-ND
C502: 4,7uF; c_1206POL; Digikey# 399-9717-1-ND
D501: SMAJ5.0A; DO-214AC_SMA; Digikey# SMAJ5.0ABCT-ND
FB501: BLM18KG221SN1D; fb_0603; Digikey# 490-5255-1-ND
FB502: MMZ1608B601C; fb_0603; Digikey# 445-2166-1-ND
J502: USB OTG; USB_MicroAB; Digikey# H11635TR-ND
R501, R502: 10k; r_0603; Digikey# 311-10KGRCT-ND
TR501: SRF2012; Digikey# SRF2012-900YCT-ND
U501: MIC2025-2YM; SOIC-8; Digikey# 576-1058-ND
U502: PRTR5V0U2X; SOT-143-4; Digikey# CM1213A-02SROSCT-ND

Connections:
+5V: C501.1, U501.7 (IN); also elsewhere on the board
/CPU/USB_DM: TR501.3, U502.2 (I/O); also elsewhere on the board
/CPU/USB_DP: TR501.2, U502.3 (I/O); also elsewhere on the board
/CPU/USB_ID: D501.2 (K), J502.4 (USB_ID); also elsewhere on the board
/Fuente/USB_VBUS: C502.1, C503.1, FB501.1, U501.6 (OUT), U501.8 (OUT), U502.4 (VCC); also elsewhere on the board
/USB OTG/CHS_OTG: D501.1 (A), FB502.2, J502.6 (S2), J502.7 (S1), J502.8 (S3), J502.9 (S4), U502.1 (GND)
/USB OTG/USB0_PPWR: R501.2, U501.1 (EN); also elsewhere on the board
/USB OTG/USB0_PWR_FAULT: R502.2, U501.2 (FLG); also elsewhere on the board
/USB OTG/USB_DM_OTG: J502.2 (USB_DN), TR501.4
/USB OTG/USB_DP_OTG: J502.3 (USB_DP), TR501.1
GND: C501.2, C502.2, C503.2, FB502.1, J502.5 (GND), R501.1, U501.3 (GND); also elsewhere on the board
unnamed: FB501.2, J502.1 (VBUS)

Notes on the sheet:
USB OTG
Par diferencial 90 ohm
FERRITE entre SHIELD y GND: para evitar que el ruido de GND salga por SHIELD hacia el exterior. Este ferrite puede reemplazarse por un resistor de 0 ohm en caso de que la placa pase los tests de EMI. CHOKE MODO COMUN: Para disminuir EMI y bajar el nivel de ruido. Solo deben usarse si la placa no pa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
POWER SWITCH
ESD PROTECTION
